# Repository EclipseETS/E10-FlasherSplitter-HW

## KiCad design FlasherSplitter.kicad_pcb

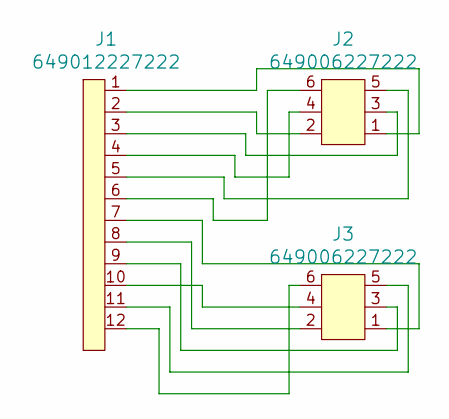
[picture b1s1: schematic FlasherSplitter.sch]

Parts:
J1: 649012227222; Manufacturer Part Number 649012227222
J2, J3: 649006227222; Manufacturer Part Number 649006227222

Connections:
unnamed: J1.1, J2.1
unnamed: J1.2, J2.2
unnamed: J1.3, J2.3
unnamed: J1.4, J2.4
unnamed: J1.5, J2.5
unnamed: J1.6, J2.6
unnamed: J1.7, J3.1
unnamed: J1.8, J3.2
unnamed: J1.9, J3.3
unnamed: J1.10, J3.4
unnamed: J1.11, J3.5
unnamed: J1.12, J3.6

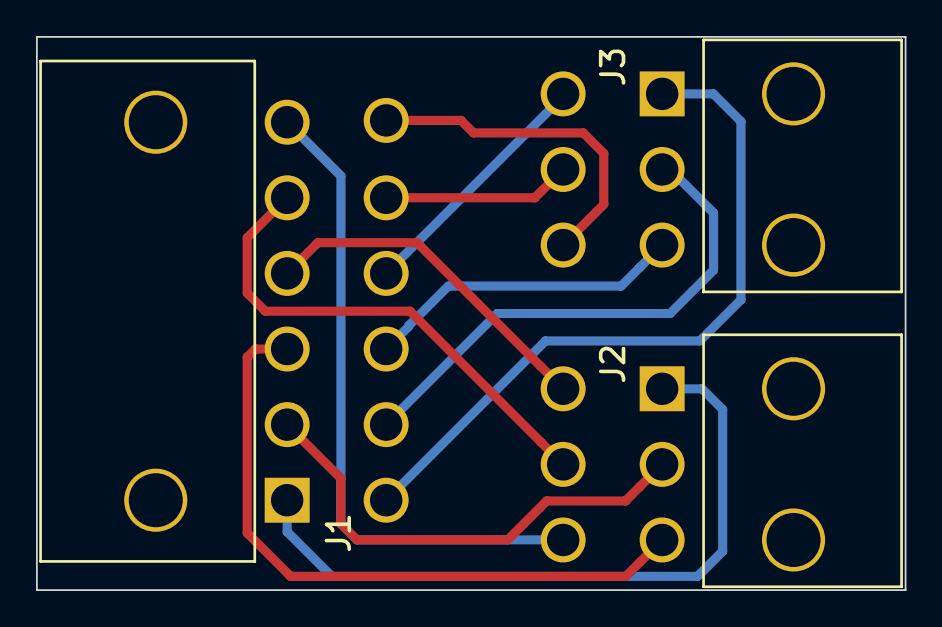
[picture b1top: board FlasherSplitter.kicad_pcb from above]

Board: 2 copper layers, 48.3 x 30.7 mm, 3 parts (0 on the bottom side), 12 nets.

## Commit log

2017-08-15 Add files from template
2017-08-21 Finish schematic and routing
